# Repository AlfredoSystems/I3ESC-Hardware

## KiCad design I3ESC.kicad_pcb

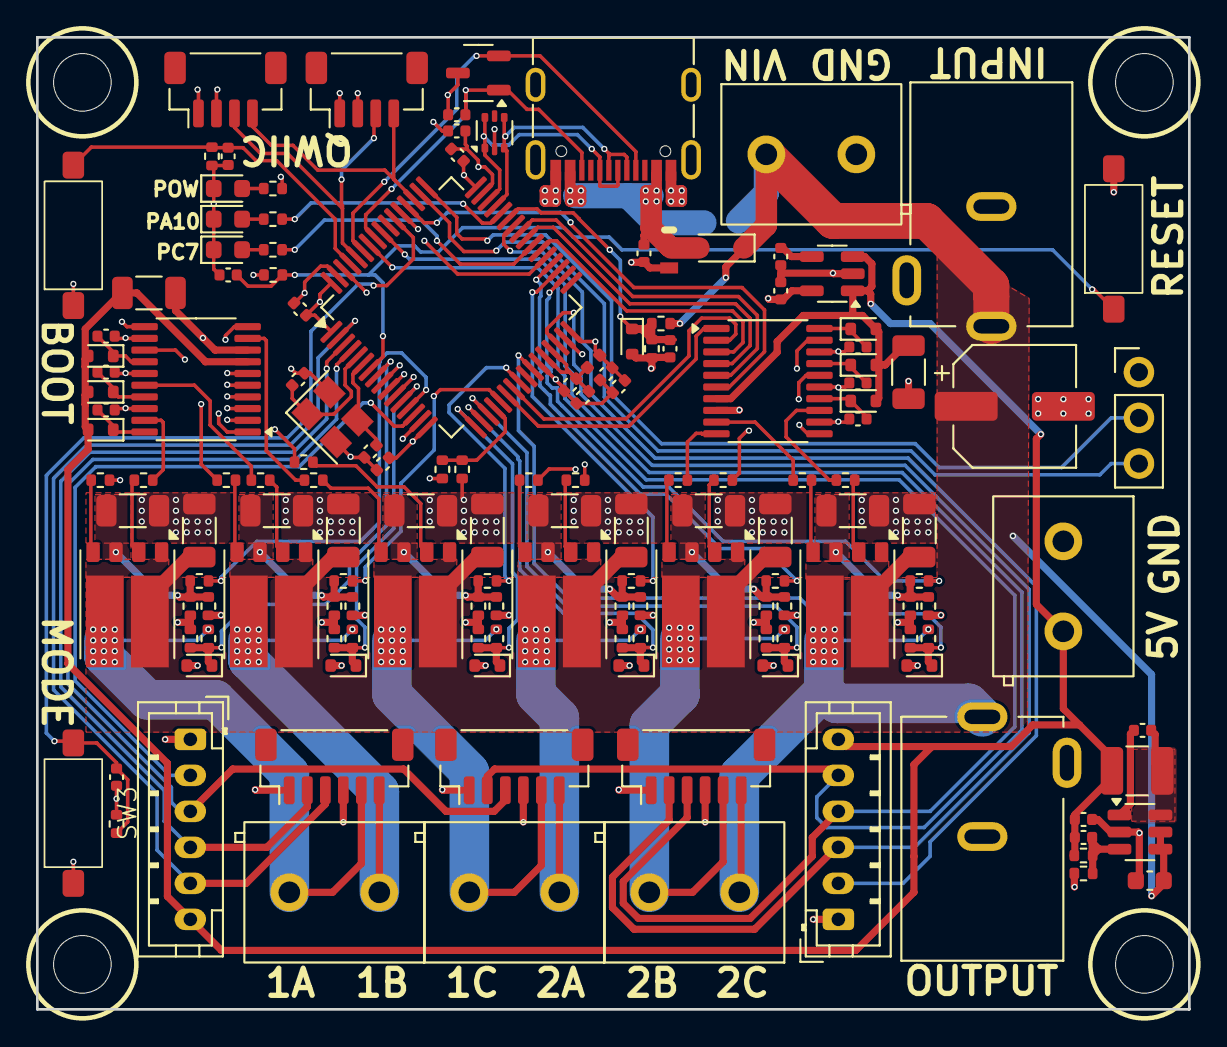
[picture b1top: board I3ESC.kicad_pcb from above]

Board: 4 copper layers, 64.0 x 54.0 mm, 155 parts (1 on the bottom side), 104 nets.

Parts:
C1, C2, C3, C41, C43, C44: 4.7uF, 50V; C_1206_3216Metric
C4, C5, C6, C21, C38, C39, C40: 1uF; C_0402_1005Metric
C7, C8, C9, C17, C23, C26, C42, C45, C46, C900: 100nF, 50V; C_0402_1005Metric
C10, C37: 10uF, 50V; C_1206_3216Metric
C11, C22: 10nF, 6.3V; C_0402_1005Metric
C12: 22pF; C_0402_1005Metric
C13, C14, C20: 2.2uF, 10V; C_0402_1005Metric
C15, C16: 15pF, 50V; C_0402_1005Metric
C18: 220uF; CP_Elec_6.3x7.7
C24, C25: 390pF; C_0402_1005Metric
C800: 2.2uF, 50V; C_0603_1608Metric
D1, D2, D3, D18, D19, D20, D42: Z3V3; D_SOD-523
D4, D5, D6, D15, D16, D17: SDM20U40-7; D_SOD-523
D7: LED_RED; LED_0603_1608Metric
D8: 1N5819; D_SOD-323
D11: ESDA6V1L; SOT-23-3
D13: ESDA25P35-1U1M; DFN1610-2
D83: LED_Blue; LED_0603_1608Metric
D84: LED_Yellow; LED_0603_1608Metric
FB1: BLM15BX601SN1D; L_0402_1005Metric
H1, H2, H3, H4: MountingHole; TGD_MountingHole
J1, J9, J12: JST SR/SZ; JST_SH_1x06_Vertical
J2, J3, J4, J6, J7: Screw_Terminal_01x02; TerminalBlock_Ningbo_2P_5mm
J5, J8: Encoder; JST_PH_B6B-PH-K_1x06_P2.00mm_Vertical
J10, J11: VIN_BARREL; DC-005C_1
J13: Conn_01x03; PinHeader_1x03_P2.54mm_Vertical
JP2: VCC-bypass; SolderJumper-2-Small
L1: 4.7uH; L_1210_3225Metric
Q1, Q2, Q3, Q4, Q5, Q6: DFN-8-2EP_6x5mm
R1, R3, R4, R6, R7, R10, R11, R12, R19, R21, R37, R38: 0R; R_0402_1005Metric
R2, R5, R8, R30, R31, R67: 1K; R_0402_1005Metric
R13, R22, R39, R44, R52, R60: 2mR; R_1206_3216Metric
R14, R23, R46, R50, R54, R62: 22K; R_0402_1005Metric
R15, R16, R18, R24, R25, R36, R42, R45, R47, R49, R51, R53, R55, R57, R58, R61, R63, R65, R66: 2K2; R_0402_1005Metric
R17, R32, R43, R48, R56, R59, R64: 15K; R_0402_1005Metric
R40: 20K; R_0402_1005Metric
R41: 10K NTC; R_0402_1005Metric
R200: 100K; R_0402_1005Metric
R300: 13K; R_0402_1005Metric
SW1, SW2, SW3: button; button-3.6x6mm
U1: SY8113BADC; TSOT-23-6
U2, U12: FD8288T (DRV8300); TSSOP-20_4.4x6.5mm_P0.65mm
U3: SPX3819M5-L-3-3; SOT-23-5
U4: STM32G474RETx; LQFP-64_10x10mm_P0.5mm
U5, U11: Qwiic; JST_SH_BM04B-SRSS-TB_1x04-1MP_P1.00mm_Vertical
U8: ABM3B-8.000MHZ; Crystal_SMD_3225-4Pin_3.2x2.5mm
U9: USB_C_Receptacle; USB_TYPE-C-31-M-12
U10: USBLC6-2P6; SOT-666

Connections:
+3V3: C7.1, C8.1, C9.1, C13.2, C20.1, C46.1, FB1.1, J1.4, J9.4, J12.4, R8.2, R14.1, R23.1, R30.1, R40.1, R46.1, R50.1, R54.1, R62.1, SW2.1, SW3.1, U3.5 (OUT), U4.1 (VBAT), U4.16 (VDD), U4.32 (VDD), U4.48 (VDD), U4.64 (VDD), U5.2 (3V3), U11.2 (3V3)
+5V: C10.1, C12.2, C14.2, C37.1, D4.2 (A), D5.2 (A), D6.2 (A), D15.2 (A), D16.2 (A), D17.2 (A), J5.6, J6.2, J8.6, L1.2, R200.1, U2.7 (GVDD), U3.1 (IN), U3.3 (EN), U12.7 (GVDD)
/IE-PHASES/IE-FETS-1A/GHx: R11.2, U2.19 (GHA)
/IE-PHASES/IE-FETS-1A/GLx: R12.2, U2.11 (GLA)
/IE-PHASES/IE-FETS-1A/SHx: C4.2, J2.2, J9.5, Q4.1 (S1), Q4.5 (D2S1), R17.2, U2.18 (SHA)
/IE-PHASES/IE-FETS-1B/GHx: R19.2, U2.16 (GHB)
/IE-PHASES/IE-FETS-1B/GLx: R21.2, U2.10 (GLB)
/IE-PHASES/IE-FETS-1B/SHx: C5.2, J2.1, J9.6, Q1.1 (S1), Q1.5 (D2S1), R32.2, U2.15 (SHB)
/IE-PHASES/IE-FETS-1C/GHx: R37.2, U2.13 (GHC)
/IE-PHASES/IE-FETS-1C/GLx: R38.2, U2.9 (GLC)
/IE-PHASES/IE-FETS-1C/SHx: C6.2, J1.5, J3.2, Q2.1 (S1), Q2.5 (D2S1), R59.2, U2.12 (SHC)
/IE-PHASES/IE-FETS-2A/GHx: R4.2, U12.19 (GHA)
/IE-PHASES/IE-FETS-2A/GLx: R6.2, U12.11 (GLA)
/IE-PHASES/IE-FETS-2A/SHx: C38.2, J1.6, J3.1, Q3.1 (S1), Q3.5 (D2S1), R48.2, U12.18 (SHA)
/IE-PHASES/IE-FETS-2B/GHx: R1.2, U12.16 (GHB)
/IE-PHASES/IE-FETS-2B/GLx: R3.2, U12.10 (GLB)
/IE-PHASES/IE-FETS-2B/SHx: C39.2, J4.2, J12.5, Q5.1 (S1), Q5.5 (D2S1), R56.2, U12.15 (SHB)
/IE-PHASES/IE-FETS-2C/GHx: R7.2, U12.13 (GHC)
/IE-PHASES/IE-FETS-2C/GLx: R10.2, U12.9 (GLC)
/IE-PHASES/IE-FETS-2C/SHx: C40.2, J4.1, J11.1, J12.6, Q6.1 (S1), Q6.5 (D2S1), R64.2, U12.12 (SHC)
/IE-USB/V_USB: C26.1, D8.2 (A), D13.1 (K), JP2.2 (B), U9.A4 (VBUS), U9.A9 (VBUS), U9.B4 (VBUS), U9.B9 (VBUS)
BOOT: C23.1, R2.1, SW2.2, U4.61 (PB8)
CC1: C25.1, D11.2 (K), U4.59 (PB6), U9.A5 (CC1)
CC2: C24.1, D11.1 (K), U4.57 (PB4), U9.B5 (CC2)
ENC_1A: J5.5, J9.3, U4.2 (PC13)
ENC_1B: J5.4, J9.2, U4.3 (PC14)
ENC_1C: J1.3, J5.3, U4.4 (PC15)
ENC_2A: J1.2, J8.5, U4.56 (PB3)
ENC_2B: J8.4, J12.3, U4.58 (PB5)
ENC_2C: J8.3, J12.2, U4.30 (PB10)
GND: C1.2, C2.2, C3.2, C7.2, C8.2, C9.2, C10.2, C11.1, C13.1, C14.1, C15.1, C16.1, C17.2, C18.2, C20.2, C21.2, C22.2, C23.2, C24.2, C25.2, C26.2, C37.2, C41.2, C42.2, C43.2, C44.2, C45.2, C46.2, C800.1, D1.2 (A), D2.2 (A), D3.2 (A), D7.1 (K), D11.3 (A), D13.2 (A), D18.2 (A), D19.2 (A), D20.2 (A), D42.2 (A), D83.1 (K), D84.1 (K), J1.1, J5.1, J6.1, J7.2, J8.1, J9.1, J10.2, J11.2, J12.1, J13.1, R2.2, R13.2, R15.2, R18.1, R22.2, R24.2, R36.1, R39.2, R41.2, R42.1, R44.2, R47.2, R49.1, R51.2, R52.2, R55.2, R57.1, R60.2, R63.2, R65.1, R66.1, R67.2, R300.2, SW1.2, U1.2 (GND), U2.8 (GND), U3.2 (GND), U4.15 (VSS), U4.27 (VSSA), U4.31 (VSS), U4.47 (VSS), U4.63 (VSS), U5.1 (GND), U8.2, U8.4, U9.A1 (GND), U9.A12 (GND), U9.B1 (GND), U9.B12 (GND), U10.2 (GND), U11.1 (GND), U12.8 (GND)
IN_H_1A: U2.1 (INHA), U4.37 (PB15)
IN_H_1B: U2.2 (INHB), U4.9 (PC1)
IN_H_1C: U2.3 (INHC), U4.10 (PC2)
IN_H_2A: U4.22 (PC4), U12.1 (INHA)
IN_H_2B: U4.23 (PC5), U12.2 (INHB)
IN_H_2C: U4.38 (PC6), U12.3 (INHC)
IN_L_1A: U2.4 (INLA), U4.53 (PC11)
IN_L_1B: U2.5 (INLB), U4.62 (PB9)
IN_L_1C: U2.6 (INLC), U4.11 (PC3)
IN_L_2A: U4.40 (PC8), U12.4 (INLA)
IN_L_2B: U4.41 (PC9), U12.5 (INLB)
IN_L_2C: U4.52 (PC10), U12.6 (INLC)
unnamed: C4.1, D4.1 (K), U2.20 (BSTA)
unnamed: C5.1, D5.1 (K), U2.17 (BSTB)
unnamed: C6.1, D6.1 (K), U2.14 (BSTC)
unnamed: D7.2 (A), R5.2
unnamed: C38.1, D15.1 (K), U12.20 (BSTA)
unnamed: C39.1, D16.1 (K), U12.17 (BSTB)
unnamed: C40.1, D17.1 (K), U12.14 (BSTC)
unnamed: D83.2 (A), R30.2
unnamed: D84.2 (A), R31.2
unnamed: Q1.2 (G1), R19.1
unnamed: Q1.4 (G2), R21.1
unnamed: Q1.3 (S2), R22.1, R23.2, R24.1, R25.1
unnamed: Q2.2 (G1), R37.1
unnamed: Q2.4 (G2), R38.1
unnamed: Q2.3 (S2), R39.1, R50.2, R51.1, R58.1
unnamed: Q3.2 (G1), R4.1
unnamed: Q3.4 (G2), R6.1
unnamed: Q3.3 (S2), R44.1, R45.1, R46.2, R47.1
unnamed: Q4.2 (G1), R11.1
unnamed: Q4.4 (G2), R12.1
unnamed: Q4.3 (S2), R13.1, R14.2, R15.1, R16.1
unnamed: Q5.2 (G1), R1.1
unnamed: Q5.4 (G2), R3.1
unnamed: Q5.3 (S2), R52.1, R53.1, R54.2, R55.1
unnamed: Q6.2 (G1), R7.1
unnamed: Q6.4 (G2), R10.1
unnamed: Q6.3 (S2), R60.1, R61.1, R62.2, R63.1
unnamed: C900.2, U1.1 (BS)
unnamed: C12.1, R200.2, R300.1, U1.3 (FB)
unnamed: C900.1, L1.1, U1.6 (LX)
unnamed: C11.2, U3.4 (BP)
unnamed: C15.2, U4.5 (PF0), U8.1
unnamed: C16.2, U4.6 (PF1), U8.3
unnamed: C17.1, R8.1, SW1.1, U4.7 (PG10)
unnamed: C21.1, C22.1, FB1.2, U4.28 (VREF+), U4.29 (VDDA)
OPAMP1_V+: R16.2, U4.13 (PA1)
OPAMP1_VOUT: J5.2, U4.14 (PA2)
OPAMP2_V+: R25.2, U4.21 (PA7)
OPAMP2_VOUT: R40.2, R41.1, U4.20 (PA6)
OPAMP3_V+: R58.2, U4.24 (PB0)
OPAMP4_V+: R45.2, U4.35 (PB13)
OPAMP4_VOUT: R61.2, U4.34 (PB12)
OPAMP5_V+: R53.2, U4.36 (PB14)
OPAMP5_VOUT: J8.2, U4.42 (PA8)
SCL: U4.51 (PA15), U5.4 (SCL), U11.4 (SCL)
SDA: U4.60 (PB7), U5.3 (SDA), U11.3 (SDA)
STM_LED1: R31.1, U4.44 (PA10)
STM_LED2: R5.1, U4.39 (PC7)
SWCLK: J13.3, U4.50 (PA14)
SWDIO: J13.2, U4.49 (PA13)
USB_D+: U4.46 (PA12), U9.A6 (D+), U9.B6 (D+), U10.1 (I/O1), U10.6 (I/O1)
USB_D-: U4.45 (PA11), U9.A7 (D-), U9.B7 (D-), U10.3 (I/O2), U10.4 (I/O2)
USER1: C45.1, R67.1, SW3.2, U4.54 (PC12)
VCC: C1.1, C2.1, C3.1, C18.1, C41.1, C43.1, C44.1, C800.2, D8.1 (K), J7.1, J10.1, JP2.1 (A), Q1.6 (D1), Q2.6 (D1), Q3.6 (D1), Q4.6 (D1), Q5.6 (D1), Q6.6 (D1), R43.2, U1.4 (EN), U1.5 (IN)
sVLT_1A: D1.1 (K), R17.1, R18.2, U4.8 (PC0)
sVLT_1B: D2.1 (K), R32.1, R36.2, U4.12 (PA0)
sVLT_1C: D3.1 (K), R59.1, R66.2, U4.17 (PA3)
sVLT_2A: D18.1 (K), R48.1, R49.2, U4.18 (PA4)
sVLT_2B: D19.1 (K), R56.1, R57.2, U4.19 (PA5)
sVLT_2C: D20.1 (K), R64.1, R65.2, U4.26 (PB2)
sVLT_VRAW: C42.1, D42.1 (K), R42.2, R43.1, U4.43 (PA9)

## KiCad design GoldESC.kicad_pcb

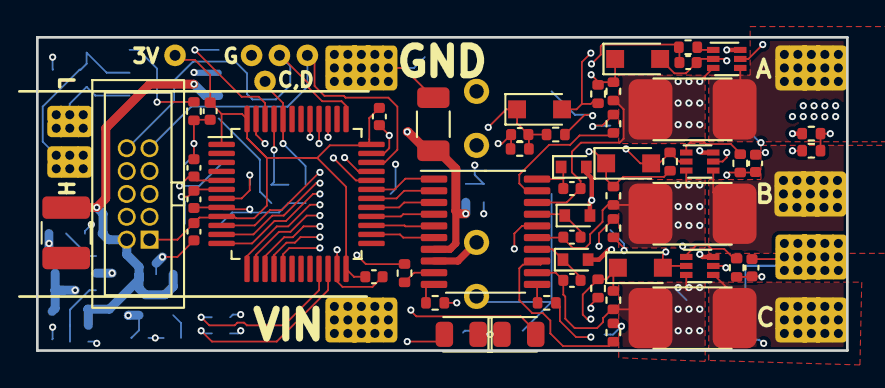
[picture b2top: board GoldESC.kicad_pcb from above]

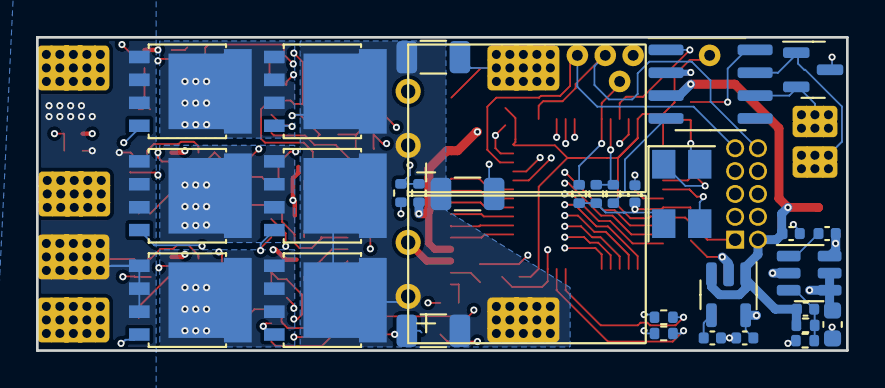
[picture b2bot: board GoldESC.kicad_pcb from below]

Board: 4 copper layers, 45.0 x 17.4 mm, 97 parts (32 on the bottom side), 68 nets.

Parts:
C1, C2, C3: 4.7uF,50V; C_1206_3216Metric
C4, C5, C6: 1uF; C_0402_1005Metric
C7, C8, C9: 4.7nF; C_0402_1005Metric
C10: 10uF,50V; C_1206_3216Metric
C40, C41: 330uF; Cap_THT_LowESR_330uF
C42, C61, C80: 100nF; C_0402_1005Metric
C52: 10nF, 6.3V; C_0402_1005Metric
C53: 2.2uF, 6.3V; C_0402_1005Metric
C60: 2.2uF, 50V; C_0603_1608Metric
C62: 22pF; C_0402_1005Metric
C63: 22uF, 10V; C_0402_1005Metric
C81, C82, C83, C84: 2.2uF; C_0402_1005Metric
C88, C89: 15pF; C_0402_1005Metric
D1, D2, D3, D42: Z3V3; D_SOD-323_HandSoldering
D4, D5, D6: SDM20U40-7; D_SOD-523
D83: LED_Red; LED_0805_2012Metric
D84: LED_Green; LED_0805_2012Metric
J1, J2, J3: PhaseOut; GE_PwrPad1
J4: GND; GE_PwrPad1
J30: CanOut; GE_SigPad_1x02
J40: Vin; GE_PwrPad1
J41: Gnd; GE_PwrPad1
J81: Conn_02x07_Counter_Clockwise; Connector_2x05_P1.27mm_IDC
L60: 4.7uH; L_1210_3225Metric
Q1, Q2, Q3, Q4, Q5, Q6: YJG150N03A; LFPAK56
R1, R2, R3: 0.5mR; GE_R_2512
R4: 2K; R_0402_1005Metric
R7: 1K; R_0402_1005Metric
R10, R11, R12, R43: 15K; R_0402_1005Metric
R13, R14, R15, R42: 2K2; R_0402_1005Metric
R16, R17, R18: 100R; R_0402_1005Metric
R19, R20, R21, R22, R23, R24: 10R; R_0402_1005Metric
R30: 5.6K; R_0402_1005Metric
R31, R80: 10K; R_0402_1005Metric
R32: 51K; R_0402_1005Metric
R40: 20K; R_0402_1005Metric
R41: 10K NTC; R_0402_1005Metric
R60: 100K; R_0402_1005Metric
R61: 13K; R_0402_1005Metric
R84, R85: 200R; R_0402_1005Metric
TP80, TP81, TP82, TP83, TP84: TestPoint; GE_TestPoint_Loop
U2: FD8288T (DRV8300); TSSOP-20_4.4x6.5mm_P0.65mm
U4, U5, U6: INA185A1; SOT-563
U30: MCP2551-I-SN; SOIC-8_3.9x4.9mm_P1.27mm
U31: CPDT-12V; SOT-23
U50: SPX3819M5-L-3-3; SOT-23-5
U60: SY8113BADC; TSOT-23-6
U80: STM32F103CBTx; LQFP-48_7x7mm_P0.5mm
U81: ABM3B-8.000MHZ; Crystal_SMD_5032-4Pin_5.0x3.2mm

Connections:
+3V3: C53.2, C81.1, C82.1, C83.1, C84.1, J81.1, TP83.1, U50.5 (OUT), U80.1 (VBAT), U80.9 (VDDA), U80.24 (VDD), U80.36 (VDD), U80.48 (VDD)
+5V: C10.1, C62.2, C63.2, D4.2 (A), D5.2 (A), D6.2 (A), J81.2, L60.2, R4.1, R40.1, R60.1, U2.7 (GVDD), U4.6 (VS), U5.6 (VS), U6.6 (VS), U30.3 (VDD), U50.1 (IN), U50.3 (EN)
/GE-Fets-A/GHx: R19.2, U2.19 (GHA)
/GE-Fets-A/GLx: R22.2, U2.11 (GLA)
/GE-Fets-A/REF_1V65: R4.2, R7.1, U4.5 (REF), U5.5 (REF), U6.5 (REF)
/GE-Fets-A/SHx: C4.2, Q1.1 (S), Q1.2 (S), Q1.3 (S), Q4.5 (D), R1.2, R10.2, U2.18 (SHA), U4.3 (IN+)
/GE-Fets-B/GHx: R20.2, U2.16 (GHB)
/GE-Fets-B/GLx: R23.2, U2.10 (GLB)
/GE-Fets-B/SHx: C5.2, Q2.1 (S), Q2.2 (S), Q2.3 (S), Q5.5 (D), R2.2, R11.2, U2.15 (SHB), U5.3 (IN+)
/GE-Fets-C/GHx: R21.2, U2.13 (GHC)
/GE-Fets-C/GLx: R24.2, U2.9 (GLC)
/GE-Fets-C/SHx: C6.2, Q3.1 (S), Q3.2 (S), Q3.3 (S), Q6.5 (D), R3.2, R12.2, U2.12 (SHC), U6.3 (IN+)
CAN_H: J30.2, U30.7 (CANH), U31.1
CAN_L: J30.1, U30.6 (CANL), U31.2
CAN_RX: R30.2, R31.1, U80.45 (PB8)
CAN_TX: U30.1 (TXD), U80.46 (PB9)
GND: C1.2, C2.2, C3.2, C7.1, C8.1, C9.1, C10.2, C40.2, C41.2, C42.2, C52.1, C53.1, C60.1, C63.1, C80.2, C81.2, C82.2, C83.2, C84.2, C88.1, C89.1, D1.2 (A), D2.2 (A), D3.2 (A), D42.2 (A), D83.1 (K), D84.1 (K), J4.1, J41.1, J81.3, Q4.1 (S), Q4.2 (S), Q4.3 (S), Q5.1 (S), Q5.2 (S), Q5.3 (S), Q6.1 (S), Q6.2 (S), Q6.3 (S), R7.2, R13.1, R14.1, R15.1, R31.2, R32.2, R41.2, R42.1, R61.2, R80.2, TP84.1, U2.8 (GND), U4.2 (GND), U5.2 (GND), U6.2 (GND), U30.2 (VSS), U31.3, U50.2 (GND), U60.2 (GND), U80.8 (VSSA), U80.23 (VSS), U80.35 (VSS), U80.47 (VSS), U81.2, U81.4
INHA: U2.1 (INHA), U80.31 (PA10)
INHB: U2.2 (INHB), U80.30 (PA9)
INHC: U2.3 (INHC), U80.29 (PA8)
INLA: U2.4 (INLA), U80.28 (PB15)
INLB: U2.5 (INLB), U80.27 (PB14)
INLC: U2.6 (INLC), U80.26 (PB13)
LimitA: J81.4, U80.39 (PB3)
LimitB: J81.6, U80.40 (PB4)
LimitC: J81.8, U80.41 (PB5)
unnamed: C4.1, D4.1 (K), U2.20 (BSTA)
unnamed: C5.1, D5.1 (K), U2.17 (BSTB)
unnamed: C6.1, D6.1 (K), U2.14 (BSTC)
unnamed: C52.2, U50.4 (BP)
unnamed: C61.1, L60.1, U60.6 (LX)
unnamed: C61.2, U60.1 (BS)
unnamed: C62.1, R60.2, R61.1, U60.3 (FB)
unnamed: C80.1, U80.7 (NRST)
unnamed: C88.2, U80.5 (PD0), U81.1
unnamed: C89.2, U80.6 (PD1), U81.3
unnamed: D83.2 (A), R84.1
unnamed: D84.2 (A), R85.1
unnamed: J1.1, R1.1, U4.4 (IN-)
unnamed: J2.1, R2.1, U5.4 (IN-)
unnamed: J3.1, R3.1, U6.4 (IN-)
unnamed: Q1.4 (G), R19.1
unnamed: Q2.4 (G), R20.1
unnamed: Q3.4 (G), R21.1
unnamed: Q4.4 (G), R22.1
unnamed: Q5.4 (G), R23.1
unnamed: Q6.4 (G), R24.1
unnamed: R16.2, U4.1 (Out)
unnamed: R17.2, U5.1 (Out)
unnamed: R18.2, U6.1 (Out)
unnamed: R30.1, U30.4 (RXD)
unnamed: R32.1, U30.8 (Rs)
unnamed: R80.1, TP80.1, U80.44 (BOOT0)
unnamed: R84.2, U80.21 (PB10)
unnamed: R85.2, U80.22 (PB11)
QuadA_USBDP: J81.7, U80.33 (PA12)
QuadB_USBDM: J81.5, U80.32 (PA11)
SWCLK: J81.10, TP81.1, U80.37 (PA14)
SWDIO: J81.9, TP82.1, U80.34 (PA13)
TEMP_FETS: R40.2, R41.1, U80.13 (PA3)
VDD: C1.1, C2.1, C3.1, C40.1, C41.1, C60.2, J40.1, Q1.5 (D), Q2.5 (D), Q3.5 (D), R43.2, U60.4 (EN), U60.5 (IN)
sCUR_A: C7.2, R16.1, U80.10 (PA0)
sCUR_B: C8.2, R17.1, U80.15 (PA5)
sCUR_C: C9.2, R18.1, U80.16 (PA6)
sVLT_A: D1.1 (K), R10.1, R13.2, U80.11 (PA1)
sVLT_B: D2.1 (K), R11.1, R14.2, U80.14 (PA4)
sVLT_C: D3.1 (K), R12.1, R15.2, U80.17 (PA7)
sVLT_VDD: C42.1, D42.1 (K), R42.2, R43.1, U80.12 (PA2)

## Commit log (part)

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2022-05-22 Added fets and drivers, initial critical components selected
2022-05-24 switched to stm32
2022-05-31 moved the Dsub off-board, most of initial layout routed
2022-05-31 GoldESC V1 ordered gerbers
2022-06-05 Updated BOM
2022-08-28 major schematic and pcb changes for production ready prototype
2022-09-01 First rev of layout before routing
2022-09-10 all nets routed for next revision, no major drc errors
2022-09-12 version for 9/10/22 jlc order
2022-11-26 updated gitignore
2024-05-22 initial copy from goldESC
2024-05-30 kicad V8
2024-06-27 updated with g431 info
2024-08-02 push before removing bldc1 external opAmps
2024-08-08 push for 8/8 order
2024-08-27 first push for v2
2024-09-02 big schematic push for stm32g474
2024-09-02 huge layout progress
2024-09-03 majority of routing for V2 completed
2024-09-07 push before schematic cleanup
2024-09-07 schematic fix before re-org
2024-09-07 cleaned up all files, created schematic PDF
2025-10-30 Refactor net naming and update component values
2026-01-22 Add decoupling capacitor to PG10 and update footprints
    Added C17 (100nF, 50V) capacitor to PG10 for improved decoupling. Updated several footprint and property fields, fixed layer and sheetname attributes, and made minor net and pad stack changes for con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
